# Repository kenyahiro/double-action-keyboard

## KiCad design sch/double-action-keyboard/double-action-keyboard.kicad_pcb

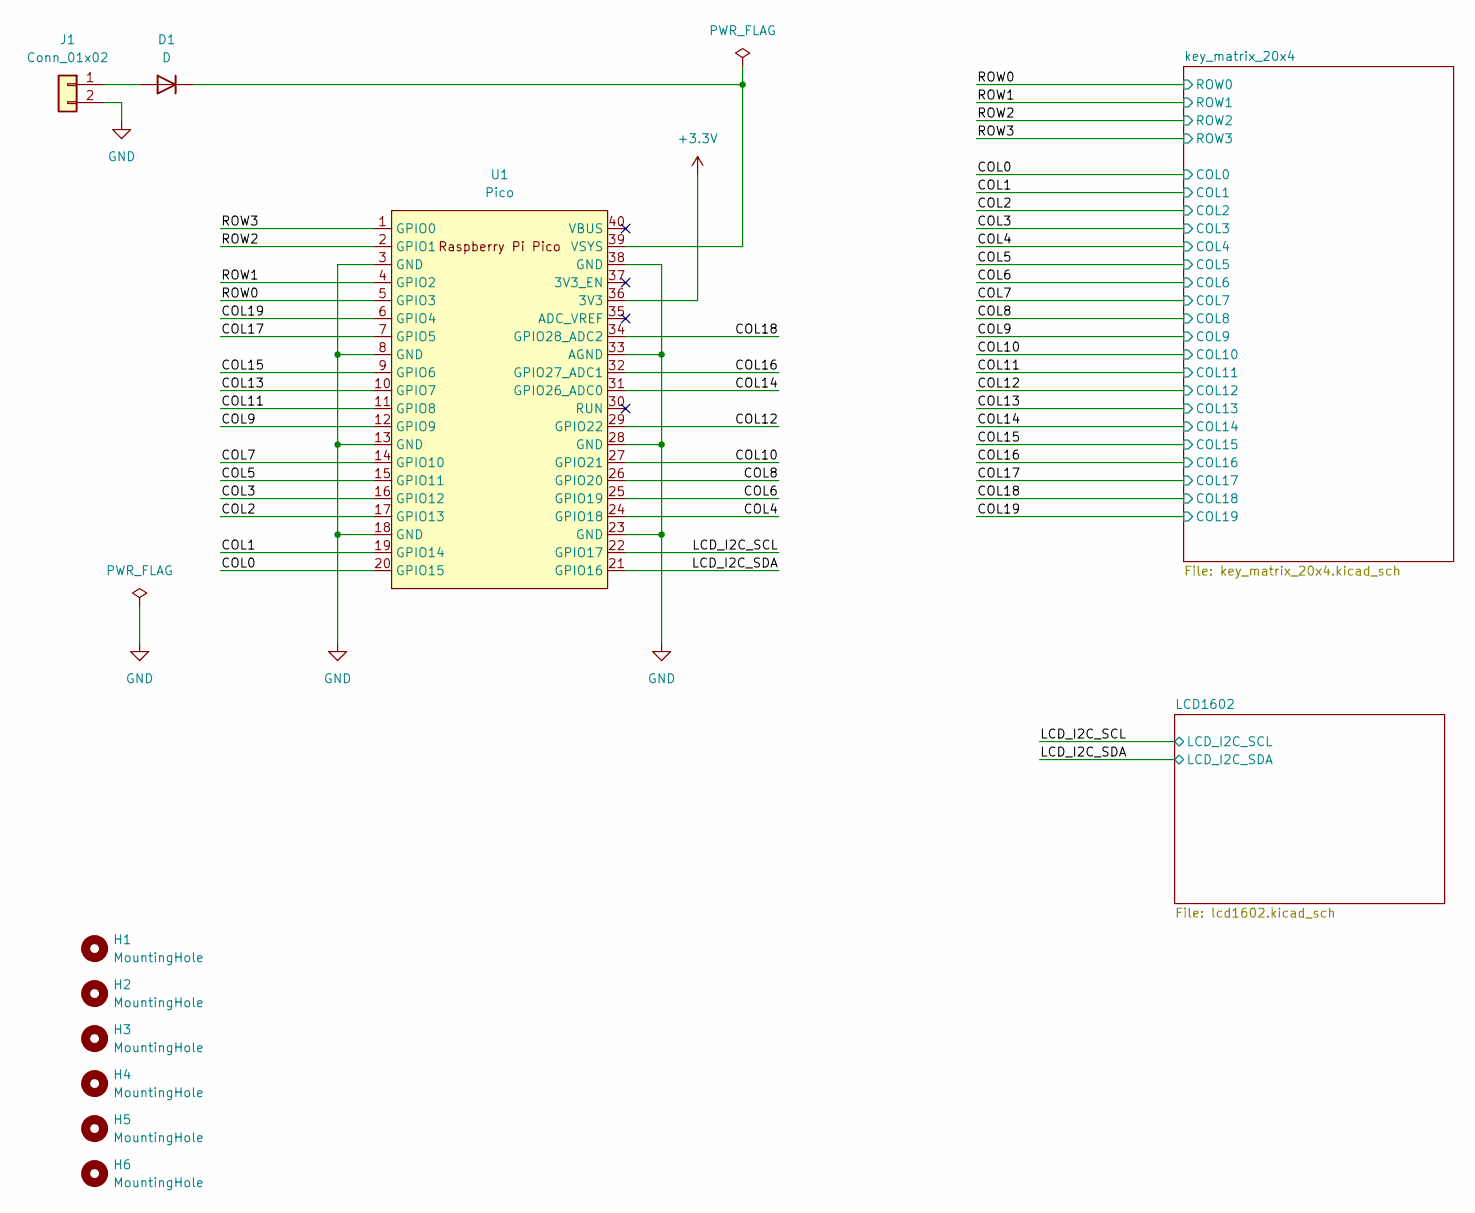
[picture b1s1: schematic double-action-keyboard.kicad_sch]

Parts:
D1: D; D_SOD-123
H1, H2, H3, H4, H5, H6: MountingHole; MountingHole_2.2mm_M2
J1: Conn_01x02; JST_PH_B2B-PH-K_1x02_P2.00mm_Vertical
U1: Pico; pico_no_dbg_smd_th

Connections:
+3.3V: U1.36 (3V3); also elsewhere on the board
/COL0: U1.20 (GPIO15); also elsewhere on the board
/COL1: U1.19 (GPIO14); also elsewhere on the board
/COL2: U1.17 (GPIO13); also elsewhere on the board
/COL3: U1.16 (GPIO12); also elsewhere on the board
/COL4: U1.24 (GPIO18); also elsewhere on the board
/COL5: U1.15 (GPIO11); also elsewhere on the board
/COL6: U1.25 (GPIO19); also elsewhere on the board
/COL7: U1.14 (GPIO10); also elsewhere on the board
/COL8: U1.26 (GPIO20); also elsewhere on the board
/COL9: U1.12 (GPIO9); also elsewhere on the board
/COL10: U1.27 (GPIO21); also elsewhere on the board
/COL11: U1.11 (GPIO8); also elsewhere on the board
/COL12: U1.29 (GPIO22); also elsewhere on the board
/COL13: U1.10 (GPIO7); also elsewhere on the board
/COL14: U1.31 (GPIO26_ADC0); also elsewhere on the board
/COL15: U1.9 (GPIO6); also elsewhere on the board
/COL16: U1.32 (GPIO27_ADC1); also elsewhere on the board
/COL17: U1.7 (GPIO5); also elsewhere on the board
/COL18: U1.34 (GPIO28_ADC2); also elsewhere on the board
/COL19: U1.6 (GPIO4); also elsewhere on the board
/LCD_I2C_SCL: U1.22 (GPIO17); also elsewhere on the board
/LCD_I2C_SDA: U1.21 (GPIO16); also elsewhere on the board
/ROW0: U1.5 (GPIO3); also elsewhere on the board
/ROW1: U1.4 (GPIO2); also elsewhere on the board
/ROW2: U1.2 (GPIO1); also elsewhere on the board
/ROW3: U1.1 (GPIO0); also elsewhere on the board
GND: J1.2, U1.3 (GND), U1.8 (GND), U1.13 (GND), U1.18 (GND), U1.23 (GND), U1.28 (GND), U1.33 (AGND), U1.38 (GND); also elsewhere on the board
unnamed: D1.2 (A), J1.1
unnamed: D1.1 (K), U1.39 (VSYS)

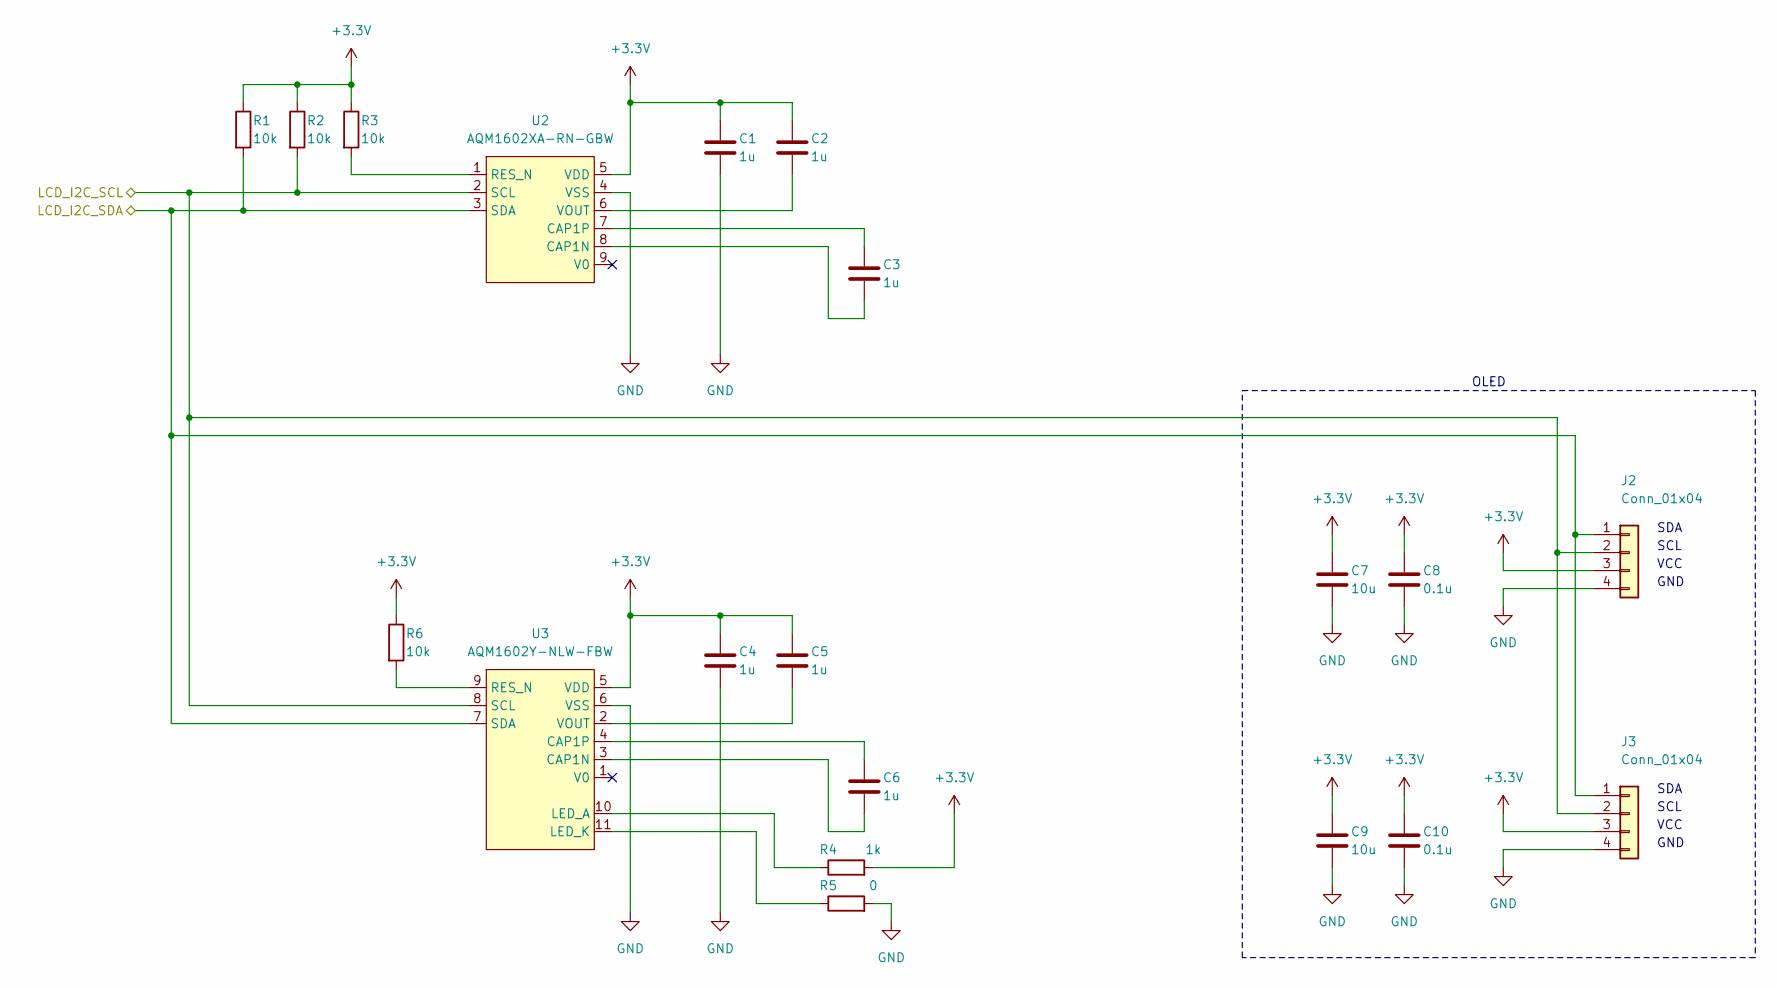
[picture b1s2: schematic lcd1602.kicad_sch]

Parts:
C1, C2, C3, C4, C5, C6: 1u; C_0603_1608Metric_Pad1.08x0.95mm_HandSolder
C7, C9: 10u; C_0603_1608Metric_Pad1.08x0.95mm_HandSolder
C8, C10: 0.1u; C_0603_1608Metric_Pad1.08x0.95mm_HandSolder
J2, J3: Conn_01x04; OLED_I2C
R1, R2, R3, R6: 10k; R_0603_1608Metric_Pad0.98x0.95mm_HandSolder
R4: 1k; R_0603_1608Metric_Pad0.98x0.95mm_HandSolder
R5: 0; R_0603_1608Metric_Pad0.98x0.95mm_HandSolder
U2: AQM1602XA-RN-GBW
U3: AQM1602Y-NLW-FBW

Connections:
+3.3V: C1.1, C2.1, C4.1, C5.1, C7.1, C8.1, C9.1, C10.1, J2.3, J3.3, R1.1, R2.1, R3.1, R4.2, R6.1, U2.5 (VDD), U3.5 (VDD); also elsewhere on the board
/LCD_I2C_SCL: J2.2, J3.2, R2.2, U2.2 (SCL), U3.8 (SCL); also elsewhere on the board
/LCD_I2C_SDA: J2.1, J3.1, R1.2, U2.3 (SDA), U3.7 (SDA); also elsewhere on the board
GND: C1.2, C4.2, C7.2, C8.2, C9.2, C10.2, J2.4, J3.4, R5.2, U2.4 (VSS), U3.6 (VSS); also elsewhere on the board
unnamed: C3.2, U2.8 (CAP1N)
unnamed: C3.1, U2.7 (CAP1P)
unnamed: R3.2, U2.1 (RES_N)
unnamed: C2.2, U2.6 (VOUT)
unnamed: C6.2, U3.3 (CAP1N)
unnamed: C6.1, U3.4 (CAP1P)
unnamed: R4.1, U3.10 (LED_A)
unnamed: R5.1, U3.11 (LED_K)
unnamed: R6.2, U3.9 (RES_N)
unnamed: C5.2, U3.2 (VOUT)

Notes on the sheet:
GND
SCL
VCC
SDA
OLED

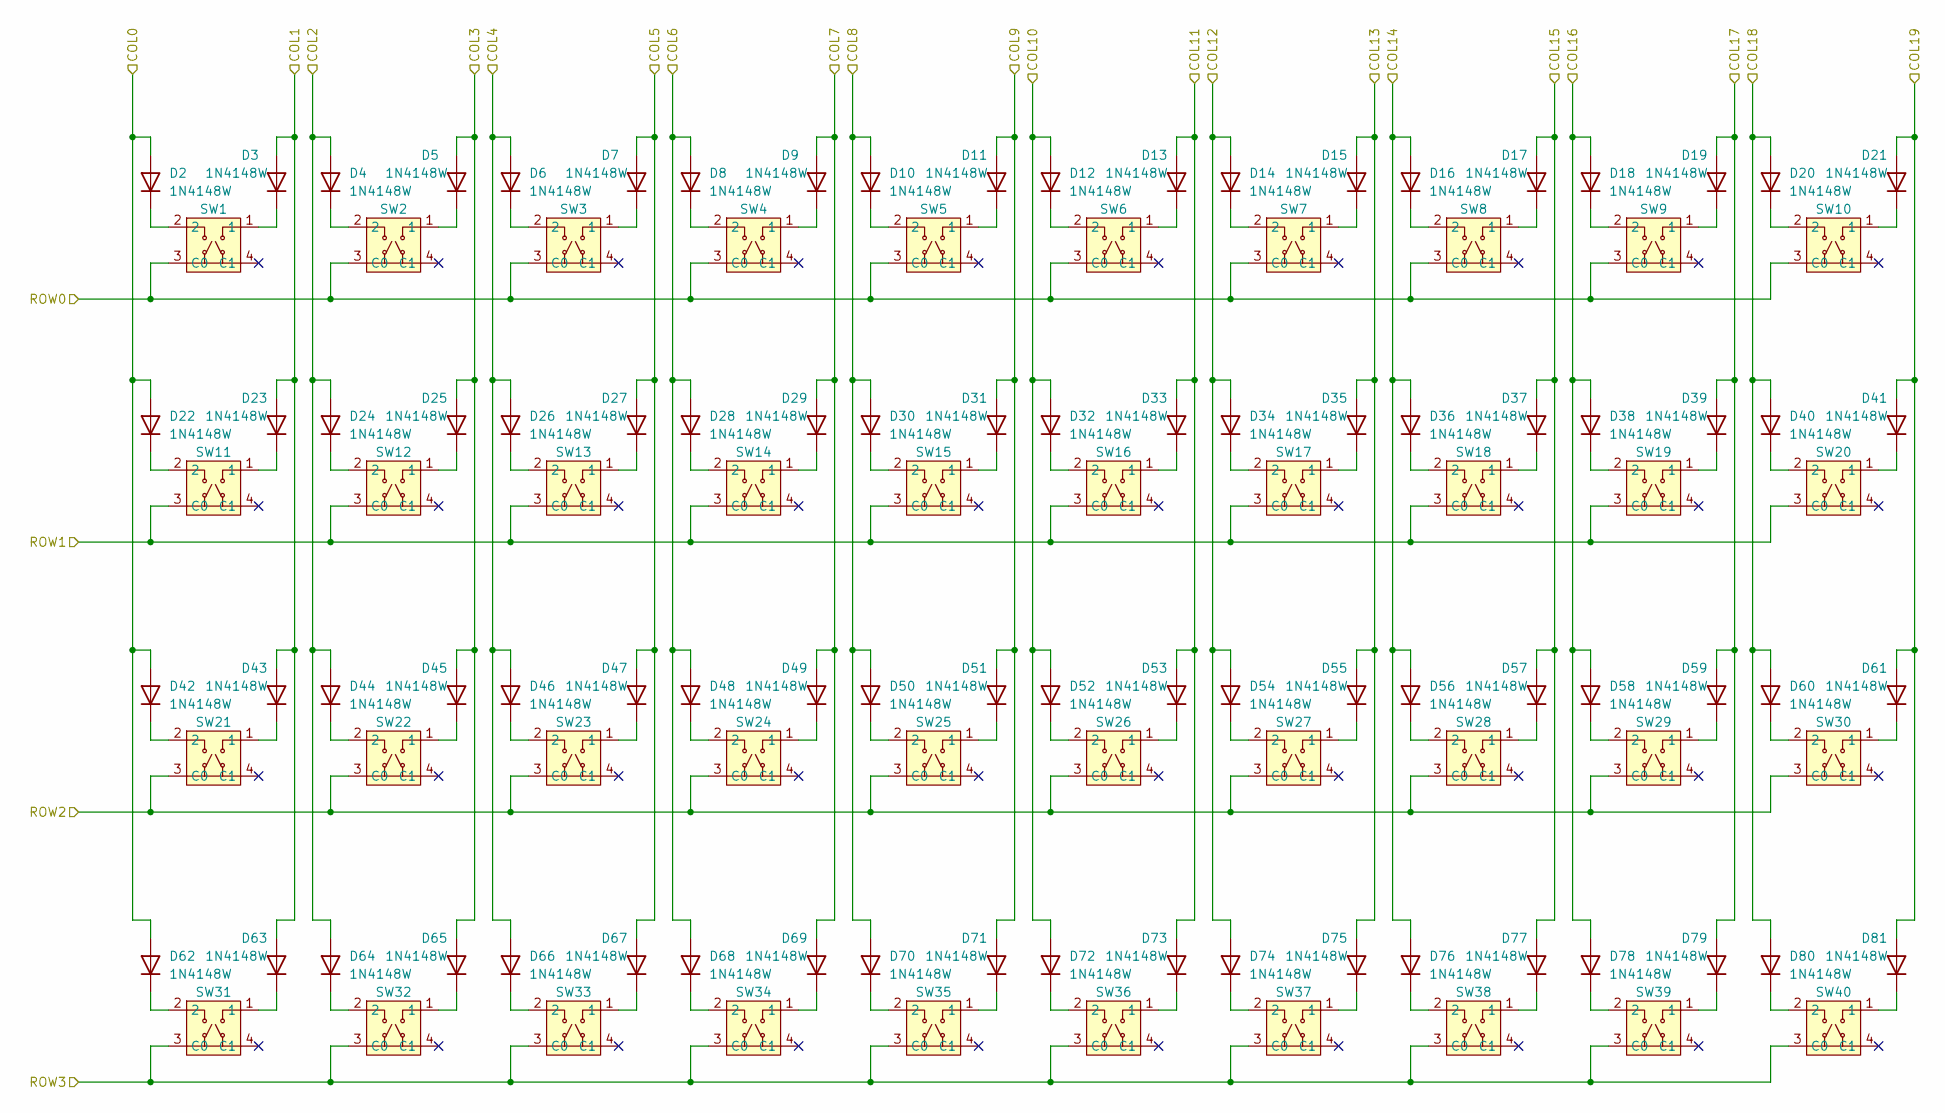
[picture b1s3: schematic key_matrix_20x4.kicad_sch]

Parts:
D2, D3, D4, D5, D6, D7, D8, D9, D10, D11, D12, D13, D14, D15, D16, D17, D18, D19, D20, D21, D22, D23, D24, D25, D26, D27, D28, D29, D30, D31, D32, D33, D34, D35, D36, D37, D38, D39, D40, D41, D42, D43, D44, D45, D46, D47, D48, D49, D50, D51, D52, D53, D54, D55, D56, D57, D58, D59, D60, D61, D62, D63, D64, D65, D66, D67, D68, D69, D70, D71, D72, D73, D74, D75, D76, D77, D78, D79, D80, D81: 1N4148W; D_SOD-123
SW1, SW2, SW3, SW4, SW5, SW6, SW7, SW8, SW9, SW10, SW11, SW12, SW13, SW14, SW15, SW16, SW17, SW18, SW19, SW20, SW21, SW22, SW23, SW24, SW25, SW26, SW27, SW28, SW29, SW30, SW31, SW32, SW33, SW34, SW35, SW36, SW37, SW38, SW39, SW40: NPS-102-668

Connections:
/COL0: D2.2 (A), D22.2 (A), D42.2 (A), D62.2 (A); also elsewhere on the board
/COL1: D3.2 (A), D23.2 (A), D43.2 (A), D63.2 (A); also elsewhere on the board
/COL2: D4.2 (A), D24.2 (A), D44.2 (A), D64.2 (A); also elsewhere on the board
/COL3: D5.2 (A), D25.2 (A), D45.2 (A), D65.2 (A); also elsewhere on the board
/COL4: D6.2 (A), D26.2 (A), D46.2 (A), D66.2 (A); also elsewhere on the board
/COL5: D7.2 (A), D27.2 (A), D47.2 (A), D67.2 (A); also elsewhere on the board
/COL6: D8.2 (A), D28.2 (A), D48.2 (A), D68.2 (A); also elsewhere on the board
/COL7: D9.2 (A), D29.2 (A), D49.2 (A), D69.2 (A); also elsewhere on the board
/COL8: D10.2 (A), D30.2 (A), D50.2 (A), D70.2 (A); also elsewhere on the board
/COL9: D11.2 (A), D31.2 (A), D51.2 (A), D71.2 (A); also elsewhere on the board
/COL10: D12.2 (A), D32.2 (A), D52.2 (A), D72.2 (A); also elsewhere on the board
/COL11: D13.2 (A), D33.2 (A), D53.2 (A), D73.2 (A); also elsewhere on the board
/COL12: D14.2 (A), D34.2 (A), D54.2 (A), D74.2 (A); also elsewhere on the board
/COL13: D15.2 (A), D35.2 (A), D55.2 (A), D75.2 (A); also elsewhere on the board
/COL14: D16.2 (A), D36.2 (A), D56.2 (A), D76.2 (A); also elsewhere on the board
/COL15: D17.2 (A), D37.2 (A), D57.2 (A), D77.2 (A); also elsewhere on the board
/COL16: D18.2 (A), D38.2 (A), D58.2 (A), D78.2 (A); also elsewhere on the board
/COL17: D19.2 (A), D39.2 (A), D59.2 (A), D79.2 (A); also elsewhere on the board
/COL18: D20.2 (A), D40.2 (A), D60.2 (A), D80.2 (A); also elsewhere on the board
/COL19: D21.2 (A), D41.2 (A), D61.2 (A), D81.2 (A); also elsewhere on the board
/ROW0: SW1.3 (C0), SW2.3 (C0), SW3.3 (C0), SW4.3 (C0), SW5.3 (C0), SW6.3 (C0), SW7.3 (C0), SW8.3 (C0), SW9.3 (C0), SW10.3 (C0); also elsewhere on the board
/ROW1: SW11.3 (C0), SW12.3 (C0), SW13.3 (C0), SW14.3 (C0), SW15.3 (C0), SW16.3 (C0), SW17.3 (C0), SW18.3 (C0), SW19.3 (C0), SW20.3 (C0); also elsewhere on the board
/ROW2: SW21.3 (C0), SW22.3 (C0), SW23.3 (C0), SW24.3 (C0), SW25.3 (C0), SW26.3 (C0), SW27.3 (C0), SW28.3 (C0), SW29.3 (C0), SW30.3 (C0); also elsewhere on the board
/ROW3: SW31.3 (C0), SW32.3 (C0), SW33.3 (C0), SW34.3 (C0), SW35.3 (C0), SW36.3 (C0), SW37.3 (C0), SW38.3 (C0), SW39.3 (C0), SW40.3 (C0); also elsewhere on the board
unnamed: D2.1 (K), SW1.2
unnamed: D3.1 (K), SW1.1
unnamed: D4.1 (K), SW2.2
unnamed: D5.1 (K), SW2.1
unnamed: D6.1 (K), SW3.2
unnamed: D7.1 (K), SW3.1
unnamed: D8.1 (K), SW4.2
unnamed: D9.1 (K), SW4.1
unnamed: D10.1 (K), SW5.2
unnamed: D11.1 (K), SW5.1
unnamed: D12.1 (K), SW6.2
unnamed: D13.1 (K), SW6.1
unnamed: D14.1 (K), SW7.2
unnamed: D15.1 (K), SW7.1
unnamed: D16.1 (K), SW8.2
unnamed: D17.1 (K), SW8.1
unnamed: D18.1 (K), SW9.2
unnamed: D19.1 (K), SW9.1
unnamed: D20.1 (K), SW10.2
unnamed: D21.1 (K), SW10.1
unnamed: D22.1 (K), SW11.2
unnamed: D23.1 (K), SW11.1
unnamed: D24.1 (K), SW12.2
unnamed: D25.1 (K), SW12.1
unnamed: D26.1 (K), SW13.2
unnamed: D27.1 (K), SW13.1
unnamed: D28.1 (K), SW14.2
unnamed: D29.1 (K), SW14.1
unnamed: D30.1 (K), SW15.2
unnamed: D31.1 (K), SW15.1
unnamed: D32.1 (K), SW16.2
unnamed: D33.1 (K), SW16.1
unnamed: D34.1 (K), SW17.2
unnamed: D35.1 (K), SW17.1
unnamed: D36.1 (K), SW18.2
unnamed: D37.1 (K), SW18.1
unnamed: D38.1 (K), SW19.2
unnamed: D39.1 (K), SW19.1
unnamed: D40.1 (K), SW20.2
unnamed: D41.1 (K), SW20.1
unnamed: D42.1 (K), SW21.2
unnamed: D43.1 (K), SW21.1
unnamed: D44.1 (K), SW22.2
unnamed: D45.1 (K), SW22.1
unnamed: D46.1 (K), SW23.2
unnamed: D47.1 (K), SW23.1
unnamed: D48.1 (K), SW24.2
unnamed: D49.1 (K), SW24.1
unnamed: D50.1 (K), SW25.2
unnamed: D51.1 (K), SW25.1
unnamed: D52.1 (K), SW26.2
unnamed: D53.1 (K), SW26.1
unnamed: D54.1 (K), SW27.2
unnamed: D55.1 (K), SW27.1
unnamed: D56.1 (K), SW28.2
unnamed: D57.1 (K), SW28.1
unnamed: D58.1 (K), SW29.2
unnamed: D59.1 (K), SW29.1
unnamed: D60.1 (K), SW30.2
unnamed: D61.1 (K), SW30.1
unnamed: D62.1 (K), SW31.2
unnamed: D63.1 (K), SW31.1
unnamed: D64.1 (K), SW32.2
unnamed: D65.1 (K), SW32.1
unnamed: D66.1 (K), SW33.2
unnamed: D67.1 (K), SW33.1
unnamed: D68.1 (K), SW34.2
unnamed: D69.1 (K), SW34.1
unnamed: D70.1 (K), SW35.2
unnamed: D71.1 (K), SW35.1
unnamed: D72.1 (K), SW36.2
unnamed: D73.1 (K), SW36.1
unnamed: D74.1 (K), SW37.2
unnamed: D75.1 (K), SW37.1
unnamed: D76.1 (K), SW38.2
unnamed: D77.1 (K), SW38.1
unnamed: D78.1 (K), SW39.2
unnamed: D79.1 (K), SW39.1
unnamed: D80.1 (K), SW40.2
unnamed: D81.1 (K), SW40.1

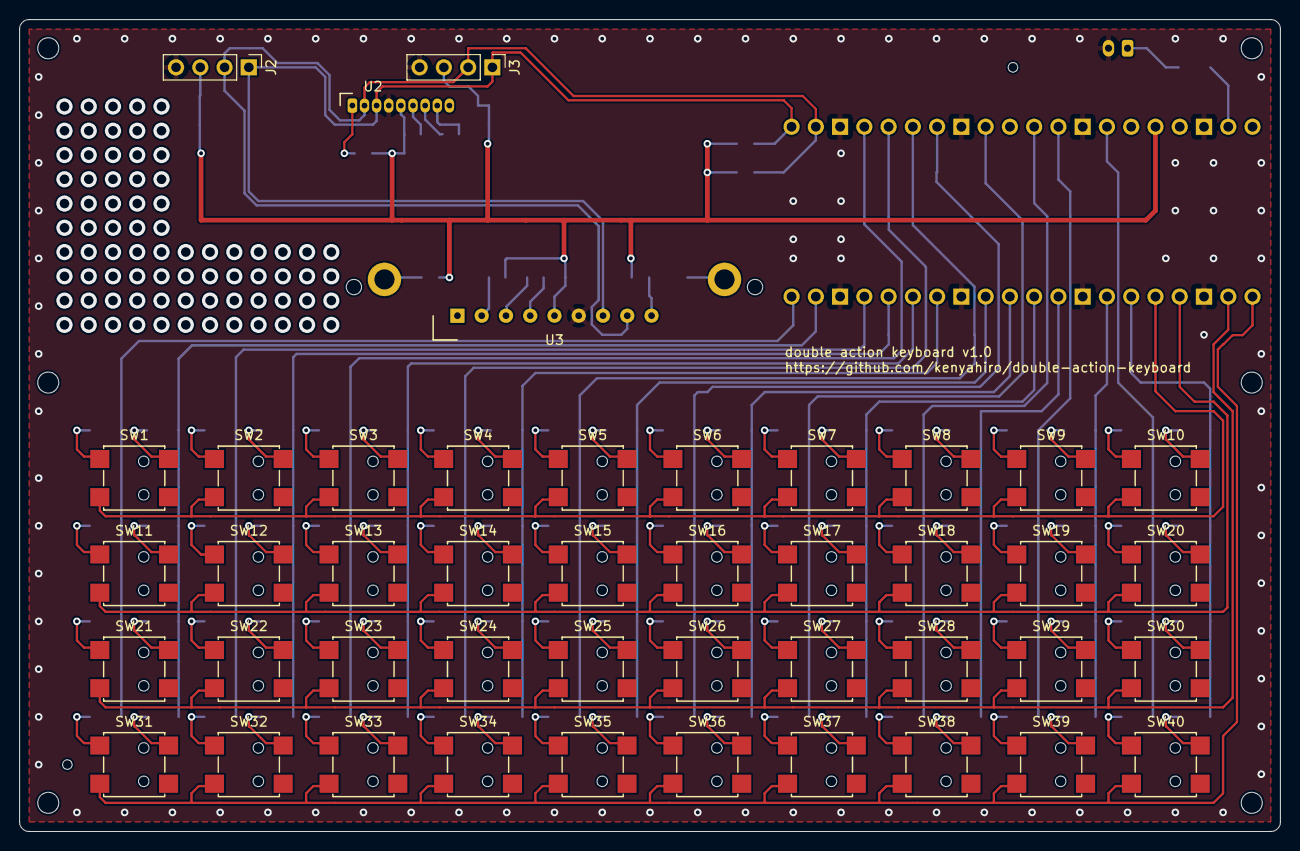
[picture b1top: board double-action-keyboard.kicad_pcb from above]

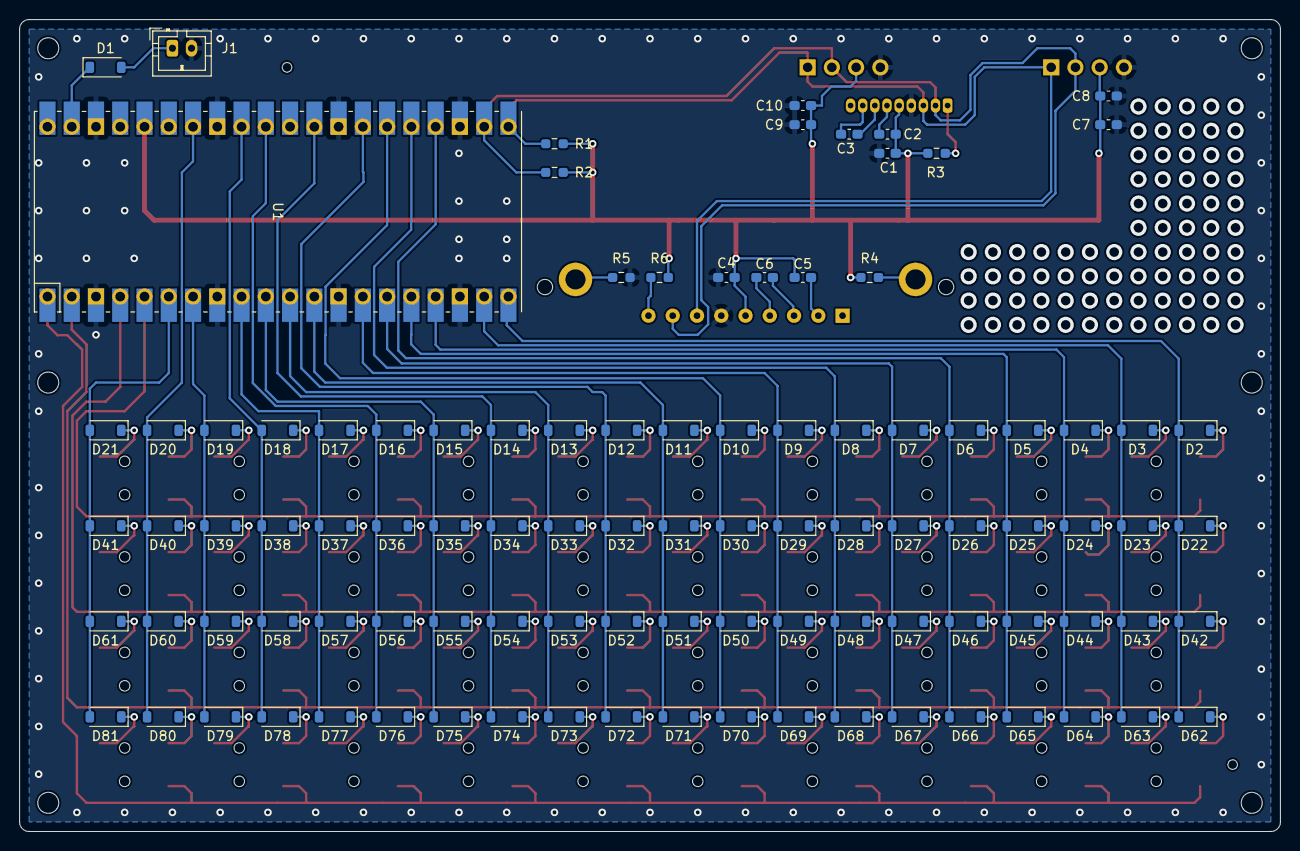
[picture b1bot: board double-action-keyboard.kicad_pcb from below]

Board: 2 copper layers, 132.0 x 85.0 mm, 149 parts (99 on the bottom side), 120 nets.

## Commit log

2023-08-04 ざっくりスイッチをつなげました。
2023-08-06 LCDを追加しました。
2023-10-10 ダイオードの配置と配線を行いました。
2024-06-07 KiCad 8.0にアップデートしました。 部品配置をやり直し中。
2024-06-07 ざっくり配線しました。 線間はもっと詰める予定。
2024-07-01 picoの位置を右側に変更しました。
2024-07-05 LCD周りの配線を行いました。
2024-07-07 ベタGNDにビアを打ちました。 空き領域にユニバーサル領域のスルーホールを追加しました。
2024-07-09 ステンシルの位置決め用穴を追加しました。
2024-07-09 JLCPCB DFM Toolのチェック結果を反映させました。
2024-07-10 LCD(小)とOLEDを同時に実装できるように位置を調整しました。 スイッチのランドを0.5mm大きくしました。
2024-11-14 スマホ一体型のケースです。 サイズ感を見るためのテスト出力になります。
2025-02-28 デバッグ時に不便なため、基板下側のケースを作ります。
